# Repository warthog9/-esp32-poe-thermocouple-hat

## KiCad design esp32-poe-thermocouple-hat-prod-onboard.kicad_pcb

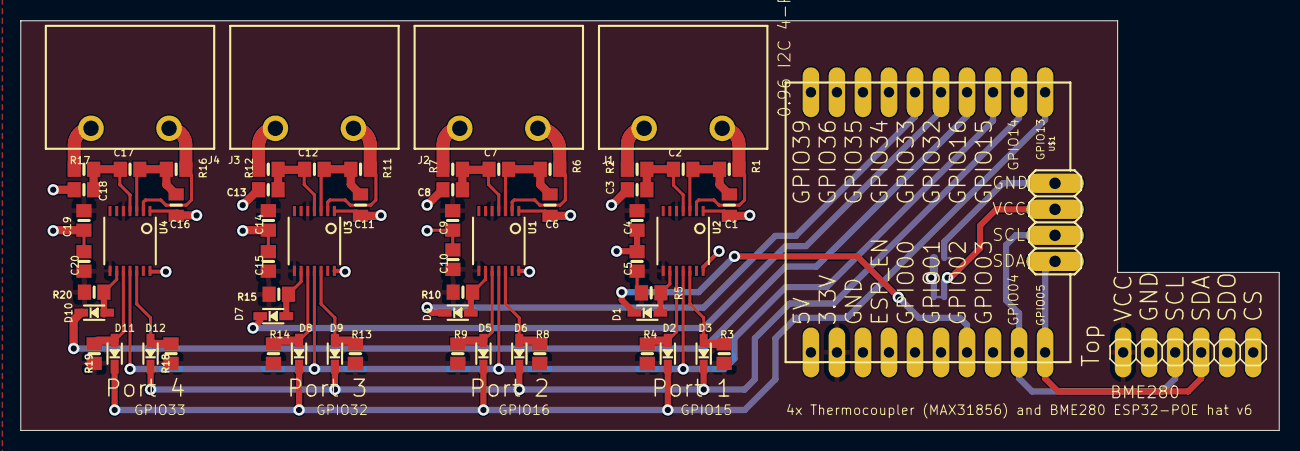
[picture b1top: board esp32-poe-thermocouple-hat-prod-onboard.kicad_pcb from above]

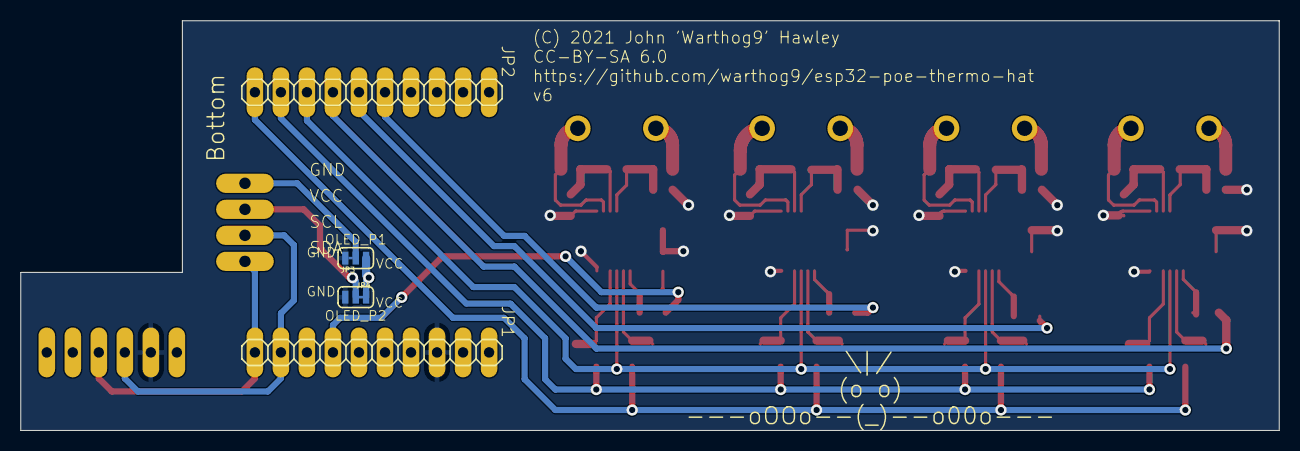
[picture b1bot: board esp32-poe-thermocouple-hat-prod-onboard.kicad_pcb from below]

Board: 2 copper layers, 122.9 x 40.0 mm, 66 parts (4 on the bottom side), 41 nets.

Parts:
BME280: 1X06
C1, C6, C11, C16: 0.01uF; 0805_10MGAP
C2, C4, C5, C7, C9, C10, C12, C14, C15, C17, C19, C20: 0.1uF; 0805-NO
C3, C8, C13, C18: 0.01uF; 0805-NO
D1, D2, D3, D4, D5, D6, D7, D8, D9, D10, D11, D12: 1N4148; SOD-323
J1, J2, J3, J4: TERMBLOCK_1X2-7.62MM-SCREW
JP1, JP2: 1X10
JP3, JP4: JUMPER-SMT_3_1-NC_TRACE_SILK; SMT-JUMPER_3_1-NC_TRACE_SILK
R1, R2, R6, R7, R11, R12, R16, R17: 100; 0805-NO
R3, R4, R5, R8, R9, R10, R13, R14, R15, R18, R19, R20: 10K; 0805-NO
U1, U2, U3, U4: MAX31856; TSSOP14
U$1: OLED-0.96-VCCGND-REVNOHOLES; OLED-I2C-4PIN-NOHOLES

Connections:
3.3V: BME280.1, C4.1, C5.1, C9.1, C10.1, C14.1, C15.1, C19.1, C20.1, JP1.2, JP3.1, JP4.3, R3.2, R4.2, R5.2, R8.2, R9.2, R10.2, R13.2, R14.2, R15.2, R18.2, R19.2, R20.2, U1.5, U1.8, U2.5, U2.8, U3.5, U3.8, U4.5, U4.8
GND: BME280.2, C1.1, C3.2, C4.2, C5.2, C6.1, C8.2, C9.2, C10.2, C11.1, C13.2, C14.2, C15.2, C16.1, C18.2, C19.2, C20.2, JP1.3, JP3.3, JP4.1, U1.1, U1.14, U2.1, U2.14, U3.1, U3.14, U4.1, U4.14
GPIO02/CS1: D1.C, JP1.7
GPIO4/SCL: BME280.3, JP1.9, U$1.3
GPIO5/SDA: BME280.4, JP1.10, U$1.4
GPIO13/SCK: D2.C, D5.C, D8.C, D11.C, JP2.10
GPIO14/MISO: D3.C, D6.C, D9.C, D12.C, JP2.9
GPIO15/MOSI: JP2.8, U1.11, U2.11, U3.11, U4.11
GPIO16/CS4: D10.C, JP2.7
GPIO32/CS3: D7.C, JP2.6
GPIO33/CS2: D4.C, JP2.5
OLED_P1: JP3.2, U$1.1
OLED_P2: JP4.2, U$1.2
SCK_3V: D2.A, R4.1, U2.10
SCK_3V1: D5.A, R9.1, U1.10
SCK_3V2: D8.A, R14.1, U3.10
SCK_3V3: D11.A, R19.1, U4.10
SDO_3V: D3.A, R3.1, U2.12
SDO_3V1: D6.A, R8.1, U1.12
SDO_3V2: D9.A, R13.1, U3.12
SDO_3V3: D12.A, R18.1, U4.12
T+1: C2.2, C3.1, R2.2, U2.4
T+2: C7.2, C8.1, R7.2, U1.4
T+3: C12.2, C13.1, R12.2, U3.4
T+4: C17.2, C18.1, R17.2, U4.4
T-1: C1.2, C2.1, R1.2, U2.3
T-2: C6.2, C7.1, R6.2, U1.3
T-3: C11.2, C12.1, R11.2, U3.3
T-4: C16.2, C17.1, R16.2, U4.3
THERM+1: J1.1, R2.1
THERM+2: J2.1, R7.1
THERM+3: J3.1, R12.1
THERM+4: J4.1, R17.1
THERM-1: J1.2, R1.1, U2.2
THERM-2: J2.2, R6.1, U1.2
THERM-3: J3.2, R11.1, U3.2
THERM-4: J4.2, R16.1, U4.2
~CS_3V1: D4.A, R10.1, U1.9
~CS_3V2: D7.A, R15.1, U3.9
~CS_3V3: D10.A, R20.1, U4.9
~CS_3V: D1.A, R5.1, U2.9

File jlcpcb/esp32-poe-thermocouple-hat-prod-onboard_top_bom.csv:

Comment,Designator,Footprint,LCSC Part #
0.1uF,C2 C4 C5 C7 C9 C10 C12 C14 C15 C17 C19 C20,0805-NO,C38141 
0.01uF,C1,0805_10MGAP,C83170 
0.01uF,C3,0805-NO,C83170 
0.01uF,C6,0805_10MGAP,C83170 
0.01uF,C8,0805-NO,C83170 
0.01uF,C11,0805_10MGAP,C83170 
0.01uF,C13,0805-NO,C83170 
0.01uF,C16,0805_10MGAP,C83170 
0.01uF,C18,0805-NO,C83170 
1N4148,D1 D2 D3 D4 D5 D6 D7 D8 D9 D10 D11 D12,SOD-323,C2128 
10K,R3 R4 R5 R8 R9 R10 R13 R14 R15 R18 R19 R20,0805-NO,C17414 
100,R1 R2 R6 R7 R11 R12 R16 R17,0805-NO,C17408 
MAX31856,U1 U2 U3 U4,TSSOP14,C2653162

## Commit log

2023-12-08 Initial commit
    Ok this is the worst initial commit I could possibly do, mostly because
    this project has literally been going for years. This is the
    culmination of a few years worth of poking around and building things.
    It's progressed from standalone sensors attached to a board to being on
    the board, different chips, etc.
    I'm using the max31856 design (prod-onboard) right now. Channel 4 is

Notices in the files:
esp32-poe-thermocouple-hat-prod-onboard.kicad_pcb:
(C) 2021 John 'Warthog9' Hawley
CC-BY-SA 6.0
